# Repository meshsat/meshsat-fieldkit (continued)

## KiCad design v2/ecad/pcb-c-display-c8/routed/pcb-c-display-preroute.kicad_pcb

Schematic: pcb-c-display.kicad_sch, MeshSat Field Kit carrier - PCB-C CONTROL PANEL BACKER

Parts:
BZ1: IP67 panel-mount sounder, 5 V DC continuous, beze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; PanelSounder
C1, C2: 10u; C_0805_2012Metric; LCSC C15850
C3, C4, C14, C15, C16: 1u; C_0603_1608Metric
C5, C6: 15p NP0; C_0402_1005Metric
C7, C8, C9, C10, C11, C12, C13, C25, C29, C38: 100n; C_0603_1608Metric
C17, C18, C26, C27: 100n; C_0603_1608Metric; LCSC C14663
C19, C20, C21, C22, C23, C24: 10n; C_0603_1608Metric; LCSC C57112
C28: 4.7u; C_0805_2012Metric
C30, C31, C32, C33, C34, C35, C36, C37: 1u 25V; C_0603_1608Metric
CAM_H1, CAM_H2: M2 screw of the USB camera module (25 x 25 board,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; MountingHole_2.2mm_M2
D1: 3 mm MWARN red, sunlight viewable; LED_D3.0mm
D2: 3 mm MCAUT amber, sunlight viewable; LED_D3.0mm
D3: 3 mm TX red (RF hazard), sunlight viewable; LED_D3.0mm
D4: 3 mm SOSACT red, sunlight viewable; LED_D3.0mm
D5: 3 mm SAT green, sunlight viewable; LED_D3.0mm
D6: 3 mm MESH green, sunlight viewable; LED_D3.0mm
D7: 3 mm LTE green, sunlight viewable; LED_D3.0mm
D8: 3 mm GPS green, sunlight viewable; LED_D3.0mm
D9: 3 mm SHORE green, sunlight viewable; LED_D3.0mm
D10: 3 mm CHG white, sunlight viewable; LED_D3.0mm
D11: 3 mm MSG white, sunlight viewable; LED_D3.0mm
D12: 3 mm BAT1 amber, sunlight viewable; LED_D3.0mm
D13: 3 mm BAT2 green, sunlight viewable; LED_D3.0mm
D14: 3 mm BAT3 green, sunlight viewable; LED_D3.0mm
D15: 3 mm BAT4 green, sunlight viewable; LED_D3.0mm
D16: 3 mm BAT5 green, sunlight viewable; LED_D3.0mm
D17: BAT54 lamp-test tie; D_SOD-123; LCSC C7502705
D18: status (GPIO25); LED_0603_1608Metric
D19: SS2040FL: EPD_SW -> VGH; D_SOD-123F
D20: SS2040FL: pump clamp; D_SOD-123F
D21: SS2040FL: pump -> VGL; D_SOD-123F
FB1, FB2, FB3, FB4: ferrite 600R; L_0603_1608Metric; LCSC C1002
H1, H2, H3, H4, H5, H6, H7, H8: M3 x 6 into the face plate's self-clinching stand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; BackerScrew_M3_GND
JP1: BOOTSEL: short while powering to enter the USB bo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; SolderJumper-2_P1.3mm_Open_RoundedPad1.0x1.5mm
JP2: PANEL_ID strap (closed = variant B); SolderJumper-2_P1.3mm_Open_RoundedPad1.0x1.5mm
J_EPD: Hirose FH34SRJ-24S-0.5SH ZIF for the E2370KS0C1 f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; Hirose_FH34SRJ-24S
J_HSJ1: U-174/U headset jack 1 (Amphenol Nexus class, dra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; PanelJack_17mm
J_HSJ2: U-174/U headset jack 2 (Amphenol Nexus class, dra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; PanelJack_17mm
J_MAINSW: MAIN button lead to A22 J_MAINSW (XH2.5 at the A2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; LeadLands_1x02
J_PANEL: panel ribbon from B16 J_PANEL (IDC 2x13 SMD, unde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; IDC-Header_2x13_P2.54mm_Vertical_SMD
J_PIJ2: PI button lead: two solder lands on the underside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; LeadLands_1x02
L1: 10uH ATNR4010100MT 0.8 A (the boost inductor); L_APV_ANR4020
Q1: AO3401A P-FET high side; SOT-23; LCSC C15127
Q2, Q3, Q4: 2N7002; SOT-23; LCSC C8545
Q5: AO3401A P-FET: the e-paper's supply switch (EPD_P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; SOT-23; LCSC C15127
Q6: Si2302CDS-T1-GE3 logic-level N-FET (Vishay, SOT-2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; SOT-23; LCSC C10488
R1, R6: 1k; R_0603_1608Metric
R2, R3: 27R; R_0603_1608Metric
R4, R42: 10k; R_0603_1608Metric
R5: 1k (BOOTSEL); R_0603_1608Metric
R7, R8: 2.2k; R_0603_1608Metric
R9, R10, R11, R12, R13, R14, R15, R16: 10k; R_0603_1608Metric; LCSC C25804
R17: 2.2k; R_0603_1608Metric; LCSC C4190
R18: 47R; R_0603_1608Metric; LCSC C23182
R19, R44: 100R; R_0603_1608Metric; LCSC C22775
R20, R38, R45: 100k; R_0603_1608Metric; LCSC C25803
R21, R22, R23, R31, R36, R40: 300R; R_0603_1608Metric; LCSC C23025
R24, R25, R26, R27, R28, R29, R30, R32, R33, R34, R35: 180R; R_0603_1608Metric; LCSC C22828
R37: 1k; R_0603_1608Metric; LCSC C21190
R39, R41: 470R; R_0603_1608Metric; LCSC C23179
R43: 0.47R 1%; R_0603_1608Metric
SW_EMCON: EMCON locking toggle (closed = TX inhibit, a hard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; ToggleBody_SPDT
SW_LIGHT: LIGHTING DAY/NIGHT/BLACKOUT toggle DPDT ON-ON-ON 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; ToggleBody_DPDT
SW_MAIN: MAIN PWR 19 mm momentary, green ring (to A22 J_MA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; PanelSwitch_19mm
SW_PI: PI 16 mm recessed momentary, amber ring (PI_SHDN_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; PanelSwitch_16mm
SW_SOS: SOS locking toggle, maintained (APEM 5636ADKB-2V,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; ToggleBody_SPDT
SW_TEST: TEST/ACK 16 mm momentary, white ring; C&K ATP16-S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; PanelSwitch_16mm
SW_ZERO: ZEROIZE locking toggle, maintained (APEM 5636ADKB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; ToggleBody_SPDT
TP1: SWCLK; TestPoint_Pad_D1.5mm
TP2: SWDIO; TestPoint_Pad_D1.5mm
TP3: C_RUN; TestPoint_Pad_D1.5mm
TP4: LED_RAIL; TestPoint_Pad_D1.5mm
TP5: LED_RAIL_SW; TestPoint_Pad_D1.5mm
TP6: +5V; TestPoint_Pad_D1.5mm
TP7: +3V3; TestPoint_Pad_D1.5mm
TP8: GND; TestPoint_Pad_D1.5mm
TP9: EXP_INT; TestPoint_Pad_D1.5mm
TP10: TX_INHIBIT_n; TestPoint_Pad_D1.5mm
TP11: EMCON_HW; TestPoint_Pad_D1.5mm
TP12: ZEROIZE_HW; TestPoint_Pad_D1.5mm
TP13: SPARE1; TestPoint_Pad_D1.5mm
TP14: SPARE2; TestPoint_Pad_D1.5mm
TP15: SPARE3; TestPoint_Pad_D1.5mm
TP16: SPARE4; TestPoint_Pad_D1.5mm
TP17: SPARE5; TestPoint_Pad_D1.5mm
TP18: SPARE6; TestPoint_Pad_D1.5mm
TP19: SPARE7; TestPoint_Pad_D1.5mm
TP20: SPARE8; TestPoint_Pad_D1.5mm
TP21: SPARE9; TestPoint_Pad_D1.5mm
TP22: SPARE10; TestPoint_Pad_D1.5mm
TP23: SPARE11; TestPoint_Pad_D1.5mm
TP24: SPARE12; TestPoint_Pad_D1.5mm
TP25: EPD_BUSY; TestPoint_Pad_D1.5mm
TP26: EPD_VGH; TestPoint_Pad_D1.5mm
TP27: EPD_VGL; TestPoint_Pad_D1.5mm
TP28: HB1; TestPoint_Pad_D1.5mm
TP29: HB2; TestPoint_Pad_D1.5mm
TP30: HB3; TestPoint_Pad_D1.5mm
TP31: SLOT_EN1; TestPoint_Pad_D1.5mm
TP32: SLOT_EN2; TestPoint_Pad_D1.5mm
TP33: SLOT_EN3; TestPoint_Pad_D1.5mm
TP34: HDMI_SEL1; TestPoint_Pad_D1.5mm
TP35: HDMI_SEL2; TestPoint_Pad_D1.5mm
TP36: PI_SHDN_REQ; TestPoint_Pad_D1.5mm
TP37: PI_KILL; TestPoint_Pad_D1.5mm
TP38: SHORE_INHIBIT; TestPoint_Pad_D1.5mm
TP39: PIJ2_A; TestPoint_Pad_D1.5mm
TP40: PIJ2_B; TestPoint_Pad_D1.5mm
U1: PCA9555PW 0x22: LED sinks, light mode inputs; TSSOP-24_4.4x7.8mm_P0.65mm; LCSC C2864778
U2: PCA9555PW 0x23: LED sinks, the battery bar, lamp 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; TSSOP-24_4.4x7.8mm_P0.65mm; LCSC C2864778
U3: RP2040 panel controller (USB device on B16's slot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; QFN-56-1EP_7x7mm_P0.4mm_EP3.2x3.2mm; LCSC C2040
U4: W25Q16JVUXIQ 16 Mbit QSPI flash (USON-8: 1 CS 2 D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; Winbond_USON-8-1EP_3x2mm_P0.5mm_EP0.2x1.6mm; LCSC C2843335
U5: TLV75533PDBV 3.3 V 500 mA LDO for the controller,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; SOT-23-5
U6, U7, U8, U10, U11: USBLC6-2SC6; SOT-23-6; LCSC C7519
U9: 74LVC1G34 non-inverting buffer (2 A 4 Y): EMCON_H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; SOT-23-5
U_LIGHT: Vishay VEML7700 ambient light sensor (1 SCL 2 VDD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; Vishay_VEML7700; LCSC C504893
Y1: 12 MHz ABM8-272-T3 (3225): 1 XIN, 3 XOUT, 2 and 4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; Crystal_SMD_3225-4Pin_3.2x2.5mm; LCSC C20625731

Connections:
/+3V3: C2.1, C4.1, C7.1, C8.1, C9.1, C10.1, C11.1, C12.1, C13.1, C16.1, C17.1, C18.1, C25.1, C38.1, Q5.2 (S), R4.2, R7.2, R8.2, R9.2, R10.2, R11.2, R12.2, R13.2, R14.2, R16.2, R42.2, TP7.1, U1.2 (A1), U1.24 (VDD), U2.2 (A1), U2.21 (A0), U2.24 (VDD), U3.1 (IOVDD), U3.10 (IOVDD), U3.22 (IOVDD), U3.33 (IOVDD), U3.42 (IOVDD), U3.43 (ADC_AVDD), U3.44 (VREG_VIN), U3.48 (USB_VDD), U3.49 (IOVDD), U4.8 (+3V3), U5.5 (+3V3), U6.5 (VBUS), U7.5 (VBUS), U8.5 (VBUS), U9.5 (+3V3), U10.5 (VBUS), U11.5 (VBUS), U_LIGHT.2 (+3V3)
/+5V: BZ1.2 (-), C1.1, C3.1, J_PANEL.1, J_PANEL.2, SW_LIGHT.2, TP6.1, U5.1 (+5V), U5.3 (+5V)
/BAT1_A: D12.2 (A), R31.2
/BAT1_K: D12.1 (K), U2.7 (IO0_3)
/BAT2_A: D13.2 (A), R32.2
/BAT2_K: D13.1 (K), U2.8 (IO0_4)
/BAT3_A: D14.2 (A), R33.2
/BAT3_K: D14.1 (K), U2.9 (IO0_5)
/BAT4_A: D15.2 (A), R34.2
/BAT4_K: D15.1 (K), U2.10 (IO0_6)
/BAT5_A: D16.2 (A), R35.2
/BAT5_K: D16.1 (K), U2.11 (IO0_7)
/BOOT_J: JP1.1 (A), R5.2
/BZ_K: BZ1.1 (+), Q4.3 (D)
/CHG_A: D10.2 (A), R29.2
/CHG_K: D10.1 (K), U1.7 (IO0_3)
/C_DVDD: C14.1, C15.1, U3.23 (DVDD), U3.45 (VREG_VOUT), U3.50 (DVDD)
/C_RUN: R4.1, TP3.1, U3.26 (RUN)
/EMCON_HW: J_PANEL.8, TP11.1, U3.32 (GPIO21), U9.4 (EMCON_HW)
/EPD_BUSY: J_EPD.9 (BUSY_N), TP25.1, U3.9 (GPIO7)
/EPD_CS: J_EPD.12 (CSB), U3.7 (GPIO5)
/EPD_DC: J_EPD.11 (DC), U3.6 (GPIO4)
/EPD_GDR: J_EPD.2 (GDR), Q6.1 (G)
/EPD_PUMP: C31.2, D20.1 (K), D21.2 (A)
/EPD_PWR_n: Q5.1 (G), R42.1, U3.41 (GPIO29_A3)
/EPD_RESE: J_EPD.3 (RESE), Q6.2 (S), R43.1
/EPD_RST: J_EPD.10 (RST_N), U3.8 (GPIO6)
/EPD_SCL: J_EPD.13 (SCL), U3.4 (GPIO2)
/EPD_SDA: J_EPD.14 (SDA), U3.5 (GPIO3)
/EPD_SW: C31.1, D19.1 (K), L1.2, Q6.3 (D)
/EPD_VCC: C28.1, C29.1, J_EPD.15 (VDDIO), J_EPD.16 (VDD), L1.1, Q5.3 (D)
/EPD_VCOM: C37.1, J_EPD.24 (VCOM)
/EPD_VDDD: C34.1, J_EPD.18 (VDDD)
/EPD_VDH: C35.1, J_EPD.20 (VDH)
/EPD_VDHR: C33.1, J_EPD.5 (VDHR)
/EPD_VDL: C36.1, J_EPD.22 (VDL)
/EPD_VGH: C30.1, D19.2 (A), J_EPD.21 (VGH), TP26.1
/EPD_VGL: C32.1, D21.1 (K), J_EPD.23 (VGL), TP27.1
/EXP_INT: J_PANEL.6, TP9.1, U1.1 (~INT), U2.1 (~INT), U3.36 (GPIO24), U8.3 (I/O2), U8.4 (I/O2)
/GPS_A: D8.2 (A), R27.2
/GPS_K: D8.1 (K), U1.11 (IO0_7)
/HB1: J_PANEL.18, TP28.1, U3.13 (GPIO10)
/HB2: J_PANEL.19, TP29.1, U3.14 (GPIO11)
/HB3: J_PANEL.20, TP30.1, U3.15 (GPIO12)
/HDMI_SEL1: J_PANEL.12, TP34.1, U3.27 (GPIO16)
/HDMI_SEL2: J_PANEL.13, TP35.1, U3.28 (GPIO17)
/LED_RAIL: Q1.3 (D), R21.1, R22.1, R23.1, R24.1, R25.1, R26.1, R27.1, R28.1, R29.1, R30.1, R31.1, R32.1, R33.1, R34.1, R35.1, R36.1, R40.1, R41.1, TP4.1
/LED_RAIL_SW: Q1.2 (S), R15.1, R17.1, R39.1, SW_LIGHT.1, TP5.1
/LED_STAT: R6.1, U3.37 (GPIO25)
/LED_STAT_A: D18.2 (A), R6.2
/LIGHT_DAY_n: C22.1, R12.1, SW_LIGHT.5, U1.13 (IO1_0)
/LIGHT_NIGHT_n: C23.1, R13.1, SW_LIGHT.6, U1.14 (IO1_1)
/LTE_A: D7.2 (A), R26.2
/LTE_K: D7.1 (K), U1.10 (IO0_6)
/MAINRING_A: R39.2, SW_MAIN.3
/MAINSW_A: FB1.1, SW_MAIN.1
/MAINSW_A2: C26.1, FB1.2, J_MAINSW.1, U10.1 (I/O1), U10.6 (I/O1)
/MAINSW_B: FB2.1, SW_MAIN.2
/MAINSW_B2: C26.2, FB2.2, J_MAINSW.2, U10.3 (I/O2), U10.4 (I/O2)
/MCAUT_A: D2.2 (A), R22.2
/MCAUT_K: D2.1 (K), U1.6 (IO0_2)
/MESH_A: D6.2 (A), R25.2
/MESH_K: D6.1 (K), U1.9 (IO0_5)
/MSG_A: D11.2 (A), R30.2
/MSG_K: D11.1 (K), U2.5 (IO0_1)
/MWARN_A: D1.2 (A), R21.2
/MWARN_K: D1.1 (K), U1.5 (IO0_1)
/PANEL_ID: JP2.1 (A), R16.1, U1.15 (IO1_2)
/PANEL_PWM: R19.1, U3.11 (GPIO8)
/PIJ2_A: FB3.1, SW_PI.1, TP39.1
/PIJ2_A2: C27.1, FB3.2, J_PIJ2.1, U11.1 (I/O1), U11.6 (I/O1)
/PIJ2_B: FB4.1, SW_PI.2, TP40.1
/PIJ2_B2: C27.2, FB4.2, J_PIJ2.2, U11.3 (I/O2), U11.4 (I/O2)
/PIRING_A: R40.2, SW_PI.3
/PIRING_K: SW_PI.4, U2.6 (IO0_2)
/PI_KILL: J_PANEL.25, TP37.1, U3.30 (GPIO19)
/PI_SHDN_REQ: J_PANEL.24, TP36.1, U3.29 (GPIO18)
/PWM1: R44.1, U3.12 (GPIO9)
/Q1_G: Q1.1 (G), R17.2, R18.1
/Q2_D: Q2.3 (D), R18.2
/Q2_G: Q2.1 (G), R19.2, R20.1
/Q3_G: Q3.1 (G), R37.2, R38.1
/Q4_G: Q4.1 (G), R44.2, R45.1
/QSPI_D0: U3.53 (QSPI_SD0), U4.5 (QSPI_D0)
/QSPI_D1: U3.55 (QSPI_SD1), U4.2 (QSPI_D1)
/QSPI_D2: U3.54 (QSPI_SD2), U4.3 (QSPI_D2)
/QSPI_D3: U3.51 (QSPI_SD3), U4.7 (QSPI_D3)
/QSPI_SCLK: U3.52 (QSPI_SCLK), U4.6 (QSPI_SCLK)
/QSPI_SS: R5.1, U3.56 (QSPI_SS_N), U4.1 (QSPI_SS)
/RAIL_SENSE: R15.2, U3.38 (GPIO26_A0)
/SAT_A: D5.2 (A), R24.2
/SAT_K: D5.1 (K), U1.8 (IO0_4)
/SCL: J_PANEL.5, R8.1, U1.22 (SCL), U2.22 (SCL), U3.3 (GPIO1), U7.3 (I/O2), U7.4 (I/O2), U_LIGHT.1 (SCL)
/SDA: J_PANEL.4, R7.1, U1.23 (SDA), U2.23 (SDA), U3.2 (GPIO0), U7.1 (I/O1), U7.6 (I/O1), U_LIGHT.4 (SDA)
/SHORE_A: D9.2 (A), R28.2
/SHORE_INHIBIT: J_PANEL.26, TP38.1, U3.31 (GPIO20)
/SHORE_K: D9.1 (K), U2.4 (IO0_0)
/SLOT_EN1: J_PANEL.21, TP31.1, U3.16 (GPIO13)
/SLOT_EN2: J_PANEL.22, TP32.1, U3.17 (GPIO14)
/SLOT_EN3: J_PANEL.23, TP33.1, U3.18 (GPIO15)
/SOSACT_A: D4.2 (A), R23.2
/SOSACT_K: D4.1 (K), U1.4 (IO0_0)
/SOS_SW: C19.1, R9.1, SW_SOS.1, U3.40 (GPIO28_A2)
/SPARE1: TP13.1, U1.16 (IO1_3)
/SPARE2: TP14.1, U1.17 (IO1_4)
/SPARE3: TP15.1, U1.18 (IO1_5)
/SPARE4: TP16.1, U1.19 (IO1_6)
/SPARE5: TP17.1, U1.20 (IO1_7)
/SPARE6: TP18.1, U2.14 (IO1_1)
/SPARE7: TP19.1, U2.15 (IO1_2)
/SPARE8: TP20.1, U2.16 (IO1_3)
/SPARE9: TP21.1, U2.17 (IO1_4)
/SPARE10: TP22.1, U2.18 (IO1_5)
/SPARE11: TP23.1, U2.19 (IO1_6)
/SPARE12: TP24.1, U2.20 (IO1_7)
/SWCLK: TP1.1, U3.24 (SWCLK)
/SWDIO: TP2.1, U3.25 (SWD)
/TESTRING_A: R41.2, SW_TEST.3
/TEST_SW: C21.1, R11.1, SW_TEST.1, U3.39 (GPIO27_A1)
/TR_APRS: J_PANEL.7, R37.1, U3.35 (GPIO23), U8.1 (I/O1), U8.6 (I/O1)
/TX_A: D3.2 (A), R36.2
/TX_INHIBIT_n: C24.1, J_PANEL.11, R14.1, SW_EMCON.1, TP10.1, U9.2 (TX_INHIBIT_n)
/TX_K: D3.1 (K), D17.2 (A), Q3.3 (D)
/TX_LAMPTEST: D17.1 (K), U2.13 (IO1_0)
/USB_DM_R: R3.1, U3.46 (USB_DM)
/USB_DP_R: R2.1, U3.47 (USB_DP)
/USB_PNL_N: J_PANEL.16, R3.2, U6.3 (I/O2), U6.4 (I/O2)
/USB_PNL_P: J_PANEL.15, R2.2, U6.1 (I/O1), U6.6 (I/O1)
/XIN: C5.1, U3.20 (XIN), Y1.1
/XOUT: C6.1, R1.2, Y1.3
/XOUT_R: R1.1, U3.21 (XOUT)
/ZEROIZE_HW: C20.1, J_PANEL.10, R10.1, SW_ZERO.1, TP12.1, U3.34 (GPIO22)
GND: C1.2, C2.2, C3.2, C4.2, C5.2, C6.2, C7.2, C8.2, C9.2, C10.2, C11.2, C12.2, C13.2, C14.2, C15.2, C16.2, C17.2, C18.2, C19.2, C20.2, C21.2, C22.2, C23.2, C24.2, C25.2, C28.2, C29.2, C30.2, C32.2, C33.2, C34.2, C35.2, C36.2, C37.2, C38.2, D18.1 (K), D20.2 (A), H1.1, H2.1, H3.1, H4.1, H5.1, H6.1, H7.1, H8.1, JP1.2 (B), JP2.2 (B), J_EPD.8 (BS), J_EPD.17 (VSS), J_EPD.25 (SHIELD), J_EPD.26 (SHIELD), J_PANEL.3, J_PANEL.9, J_PANEL.14, J_PANEL.17, Q2.2 (S), Q3.2 (S), Q4.2 (S), R20.2, R38.2, R43.2, R45.2, SW_EMCON.2, SW_LIGHT.4, SW_MAIN.4, SW_SOS.2, SW_TEST.2, SW_TEST.4, SW_ZERO.2, TP8.1, U1.3 (A2), U1.12 (VSS), U1.21 (A0), U2.3 (A2), U2.12 (VSS), U3.19 (TESTEN), U3.57 (GND), U4.4 (GND), U4.9 (GND), U5.2 (GND), U6.2 (GND), U7.2 (GND), U8.2 (GND), U9.3 (GND), U10.2 (GND), U11.2 (GND), U_LIGHT.3 (GND), Y1.2 (G), Y1.4 (G)

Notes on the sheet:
PCB-C CONTROL PANEL BACKER C24
RIBBON FROM B16, 5 V, 3.3 V LDO, USB AND BUS ESD, FLAGS | RP2040 PANEL CONTROLLER, FLASH, CRYSTAL, BOOTSEL, BUS PULL-UPS
RIBBON FROM B16, 5 V, 3.3 V LDO, USB AND BUS ESD, FLAGS
RP2040 PANEL CONTROLLER, FLASH, CRYSTAL, BOOTSEL, BUS PULL-UPS
page 1 of 5 MeshSat field kit V2, CERN-OHL-S-2.0 PROTOTYPE, nothing built 2026-09-17
panel ribbon from B16 J_PANEL
TLV75533PDBV 3.3 V 500 mA LDO for..
RP2040 panel controller
status
BOOTSEL
p2,5
p2,4,5
p2,3,4
p3,4
p4,5
p2,4
RP2040 PANEL CONTROLLER, FLASH, CRYSTAL, BOOTSEL, BUS PULL-UPS | EXPANDERS 0x22 / 0x23, MODE INPUTS, EMCON INVERTER, STRAPS | LED RAIL, INDICATORS, TX LAMP, SWITCHES
RP2040 PANEL CONTROLLER, FLASH, CRYSTAL, BOOTSEL, BUS PULL-UPS (continued)
EXPANDERS 0x22 / 0x23, MODE INPUTS, EMCON INVERTER, STRAPS
LED RAIL, INDICATORS, TX LAMP, SWITCHES AND LEADS
page 2 of 5 MeshSat field kit V2, CERN-OHL-S-2.0 PROTOTYPE, nothing built 2026-09-17
W25Q16JVUXIQ 16 Mbit QSPI flash
12 MHz ABM8-272-T3
PCA9555PW 0x22
PANEL_ID strap
PCA9555PW 0x23
74LVC1G34 non-inverting buffer
LIGHTING DAY/NIGHT/BLACKOUT toggle..
p1,5
p1,4,5
p1,4
p1,3,4
LED RAIL, INDICATORS, TX LAMP, SWITCHES AND LEADS (continued)
page 3 of 5 MeshSat field kit V2, CERN-OHL-S-2.0 PROTOTYPE, nothing built 2026-09-17
3 mm MWARN red
3 mm MCAUT amber
3 mm SOSACT red
3 mm SAT green
3 mm MESH green
3 mm LTE green

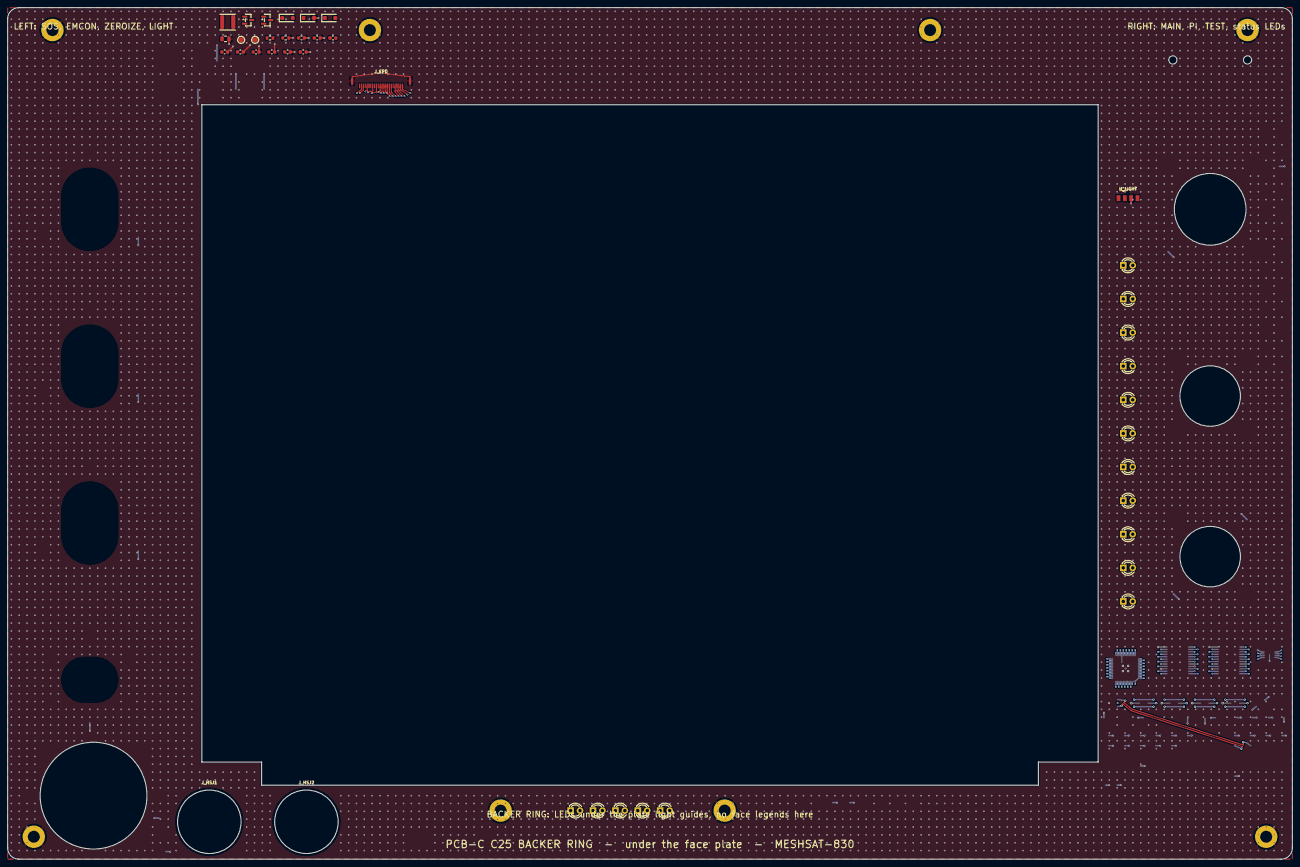
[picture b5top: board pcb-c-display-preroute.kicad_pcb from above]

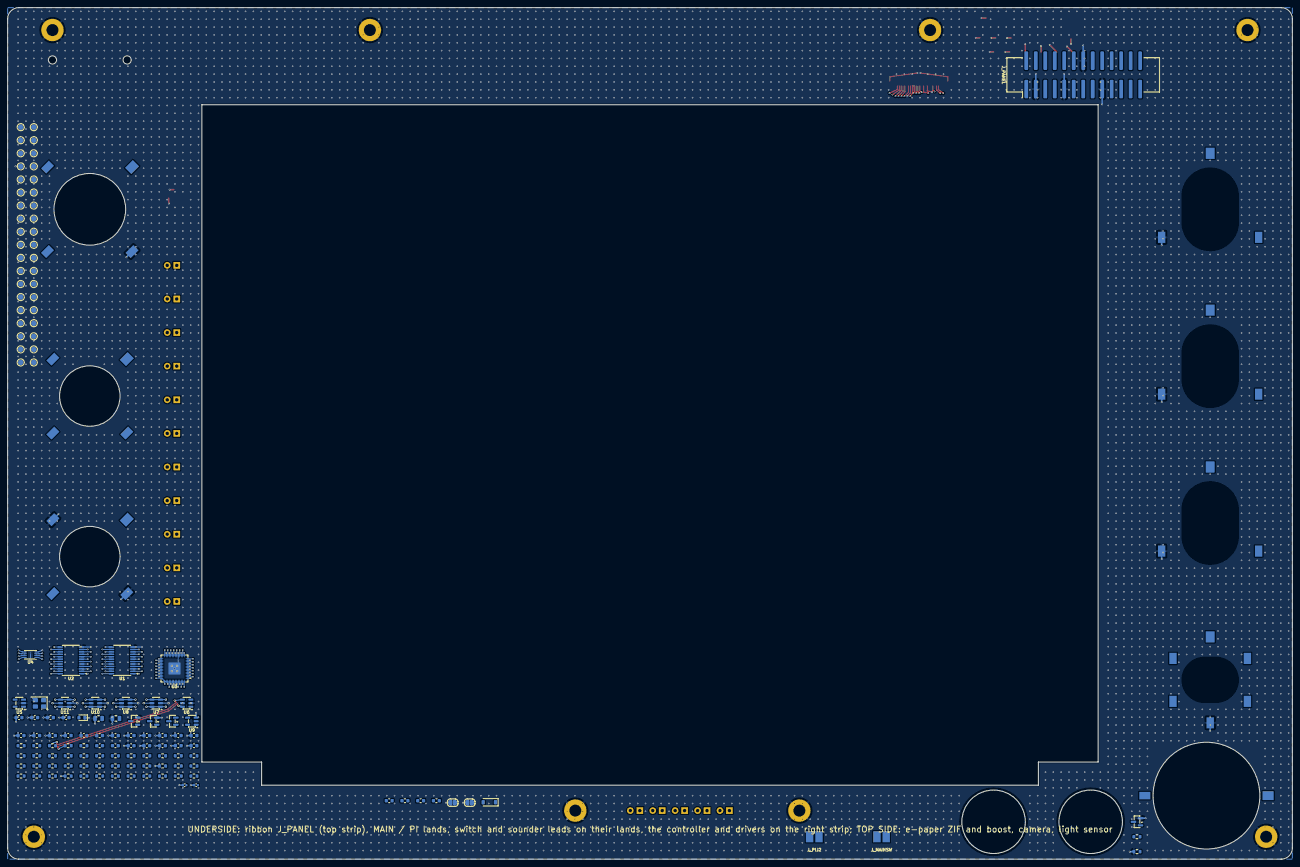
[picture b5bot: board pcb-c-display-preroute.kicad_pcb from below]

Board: 4 copper layers, 344.0 x 228.0 mm, 194 parts (135 on the bottom side), 133 nets.
